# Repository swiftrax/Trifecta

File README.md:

# Trifecta

A 65% Alice with per key RGB, RGB backlighting and 3 rotary encoders. Designed by 2Moons-JP and swiftrax

# Render

# Proto Image

## License

This repository is under the [GNU GPL V2 license](https://github.com/swiftrax/Trifecta/blob/master/LICENSE). If you plan to sell these pcbs, make sure to read it.

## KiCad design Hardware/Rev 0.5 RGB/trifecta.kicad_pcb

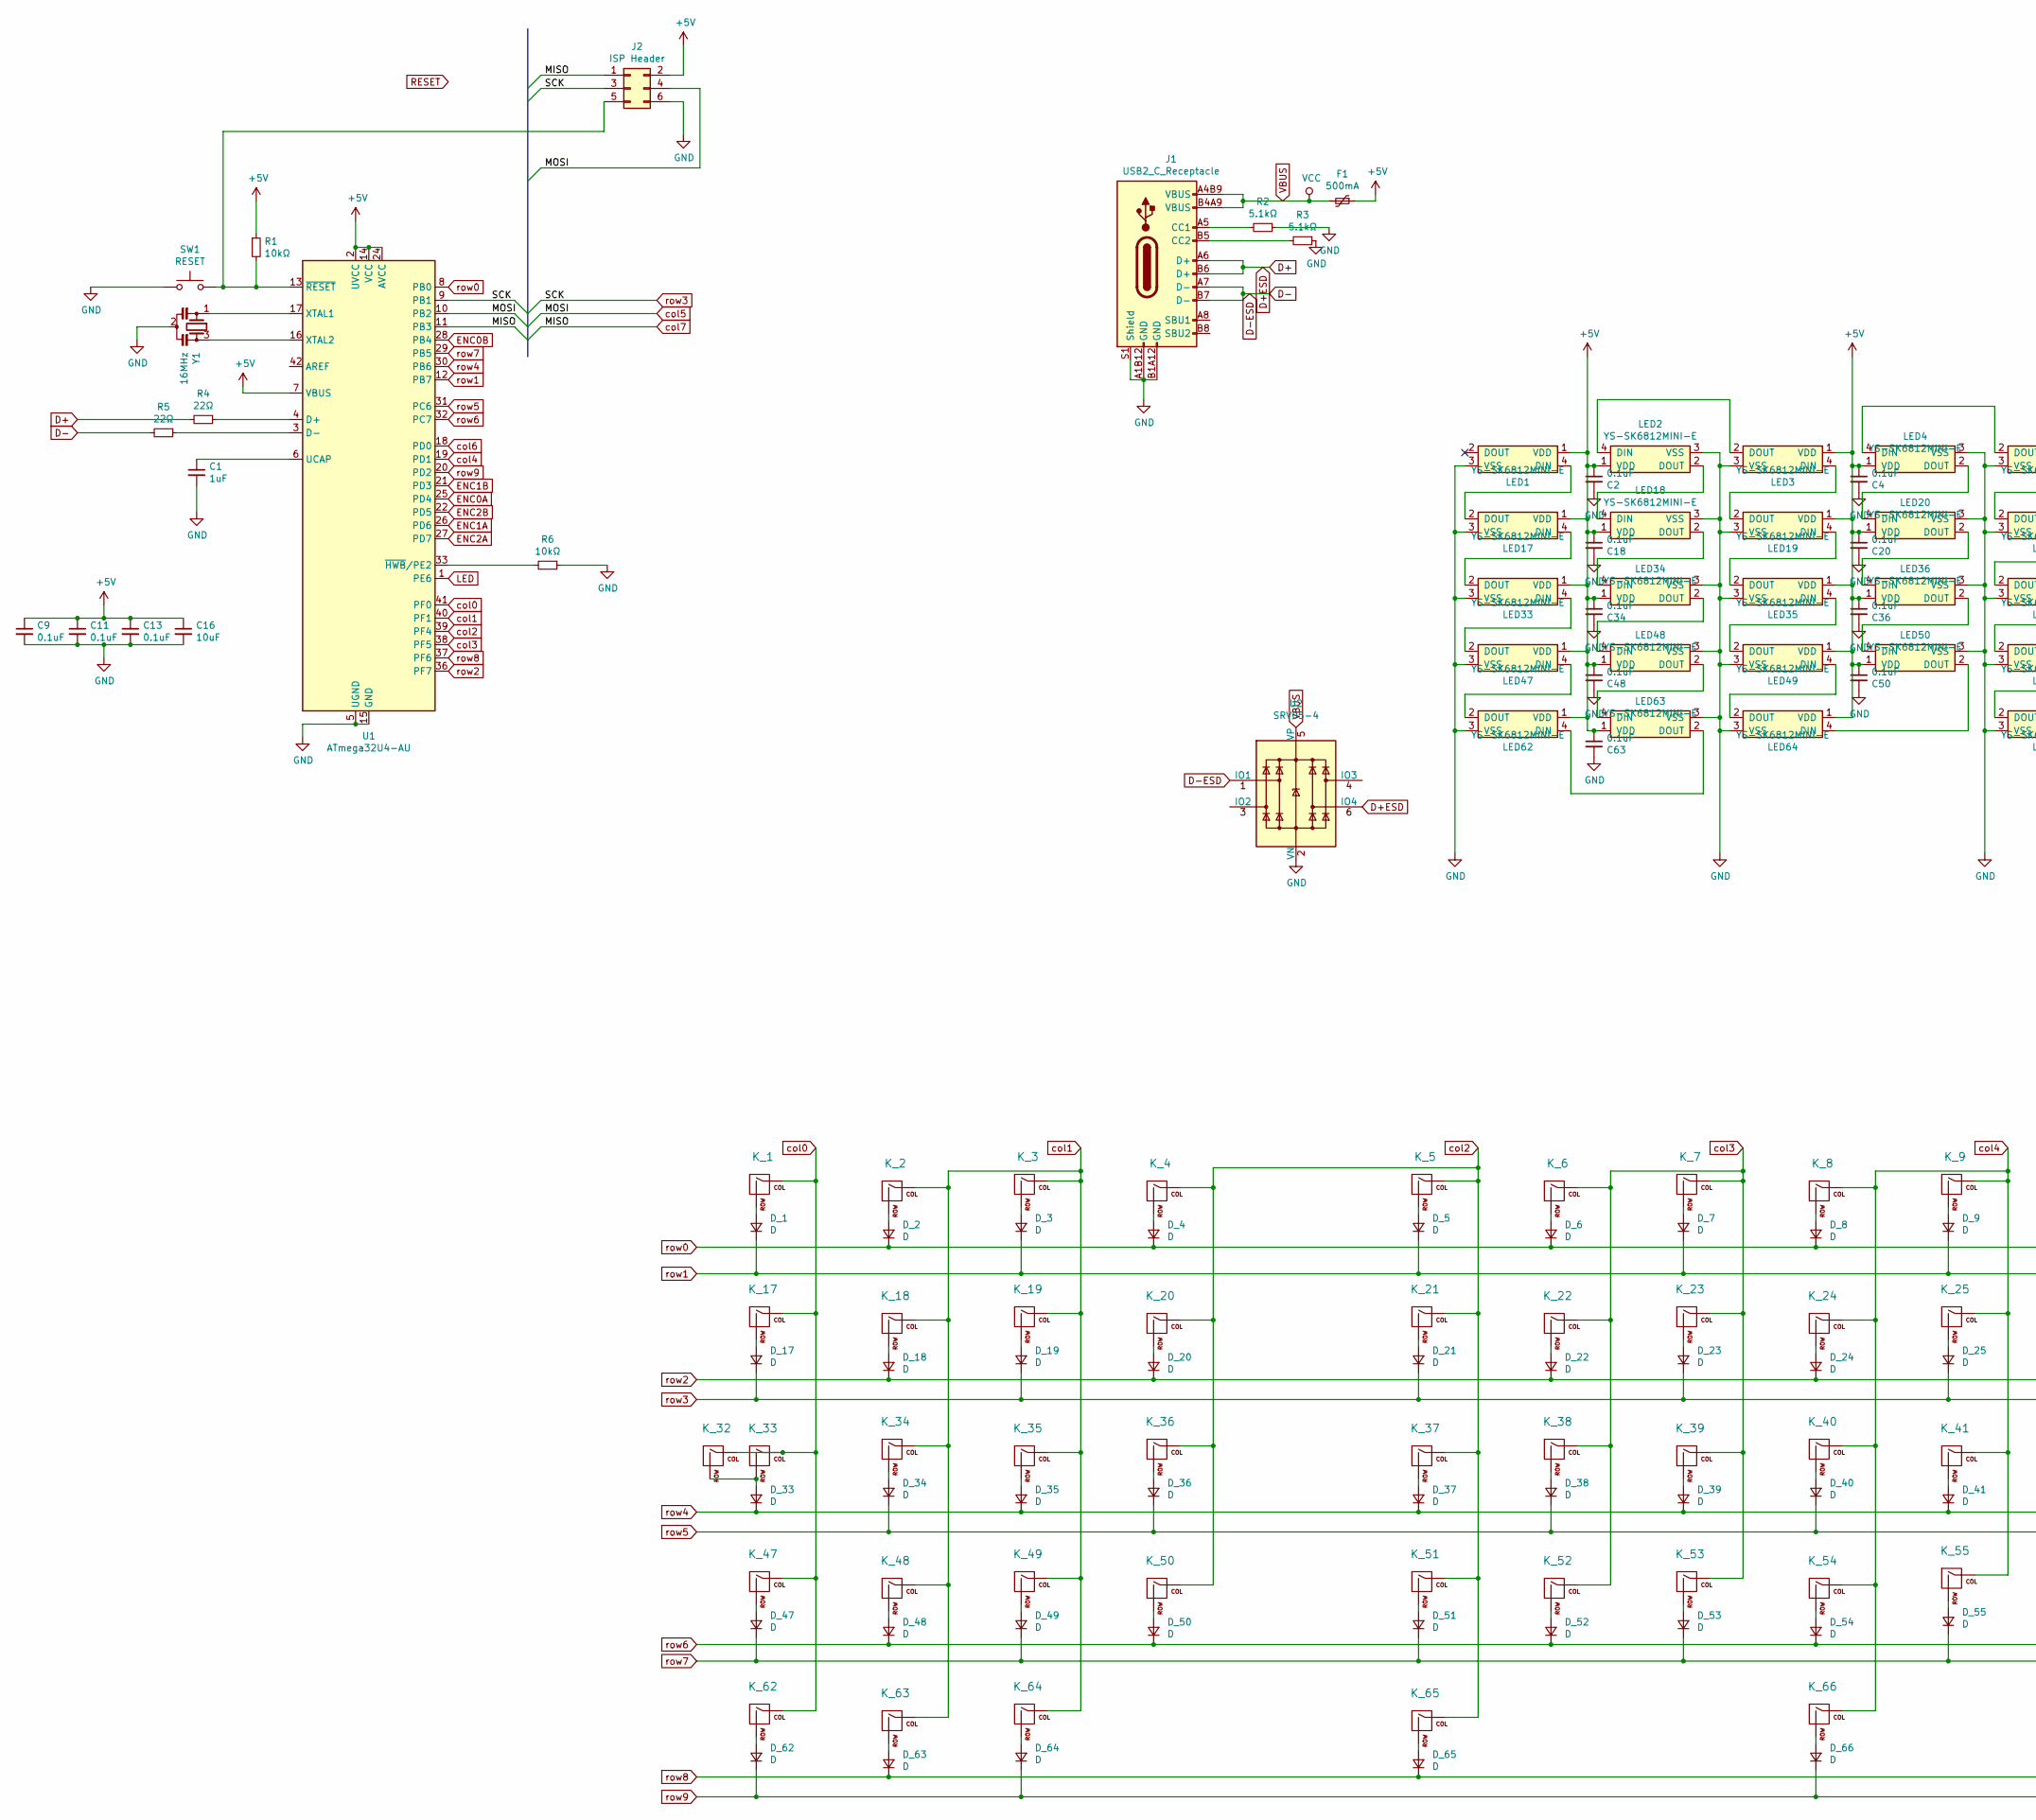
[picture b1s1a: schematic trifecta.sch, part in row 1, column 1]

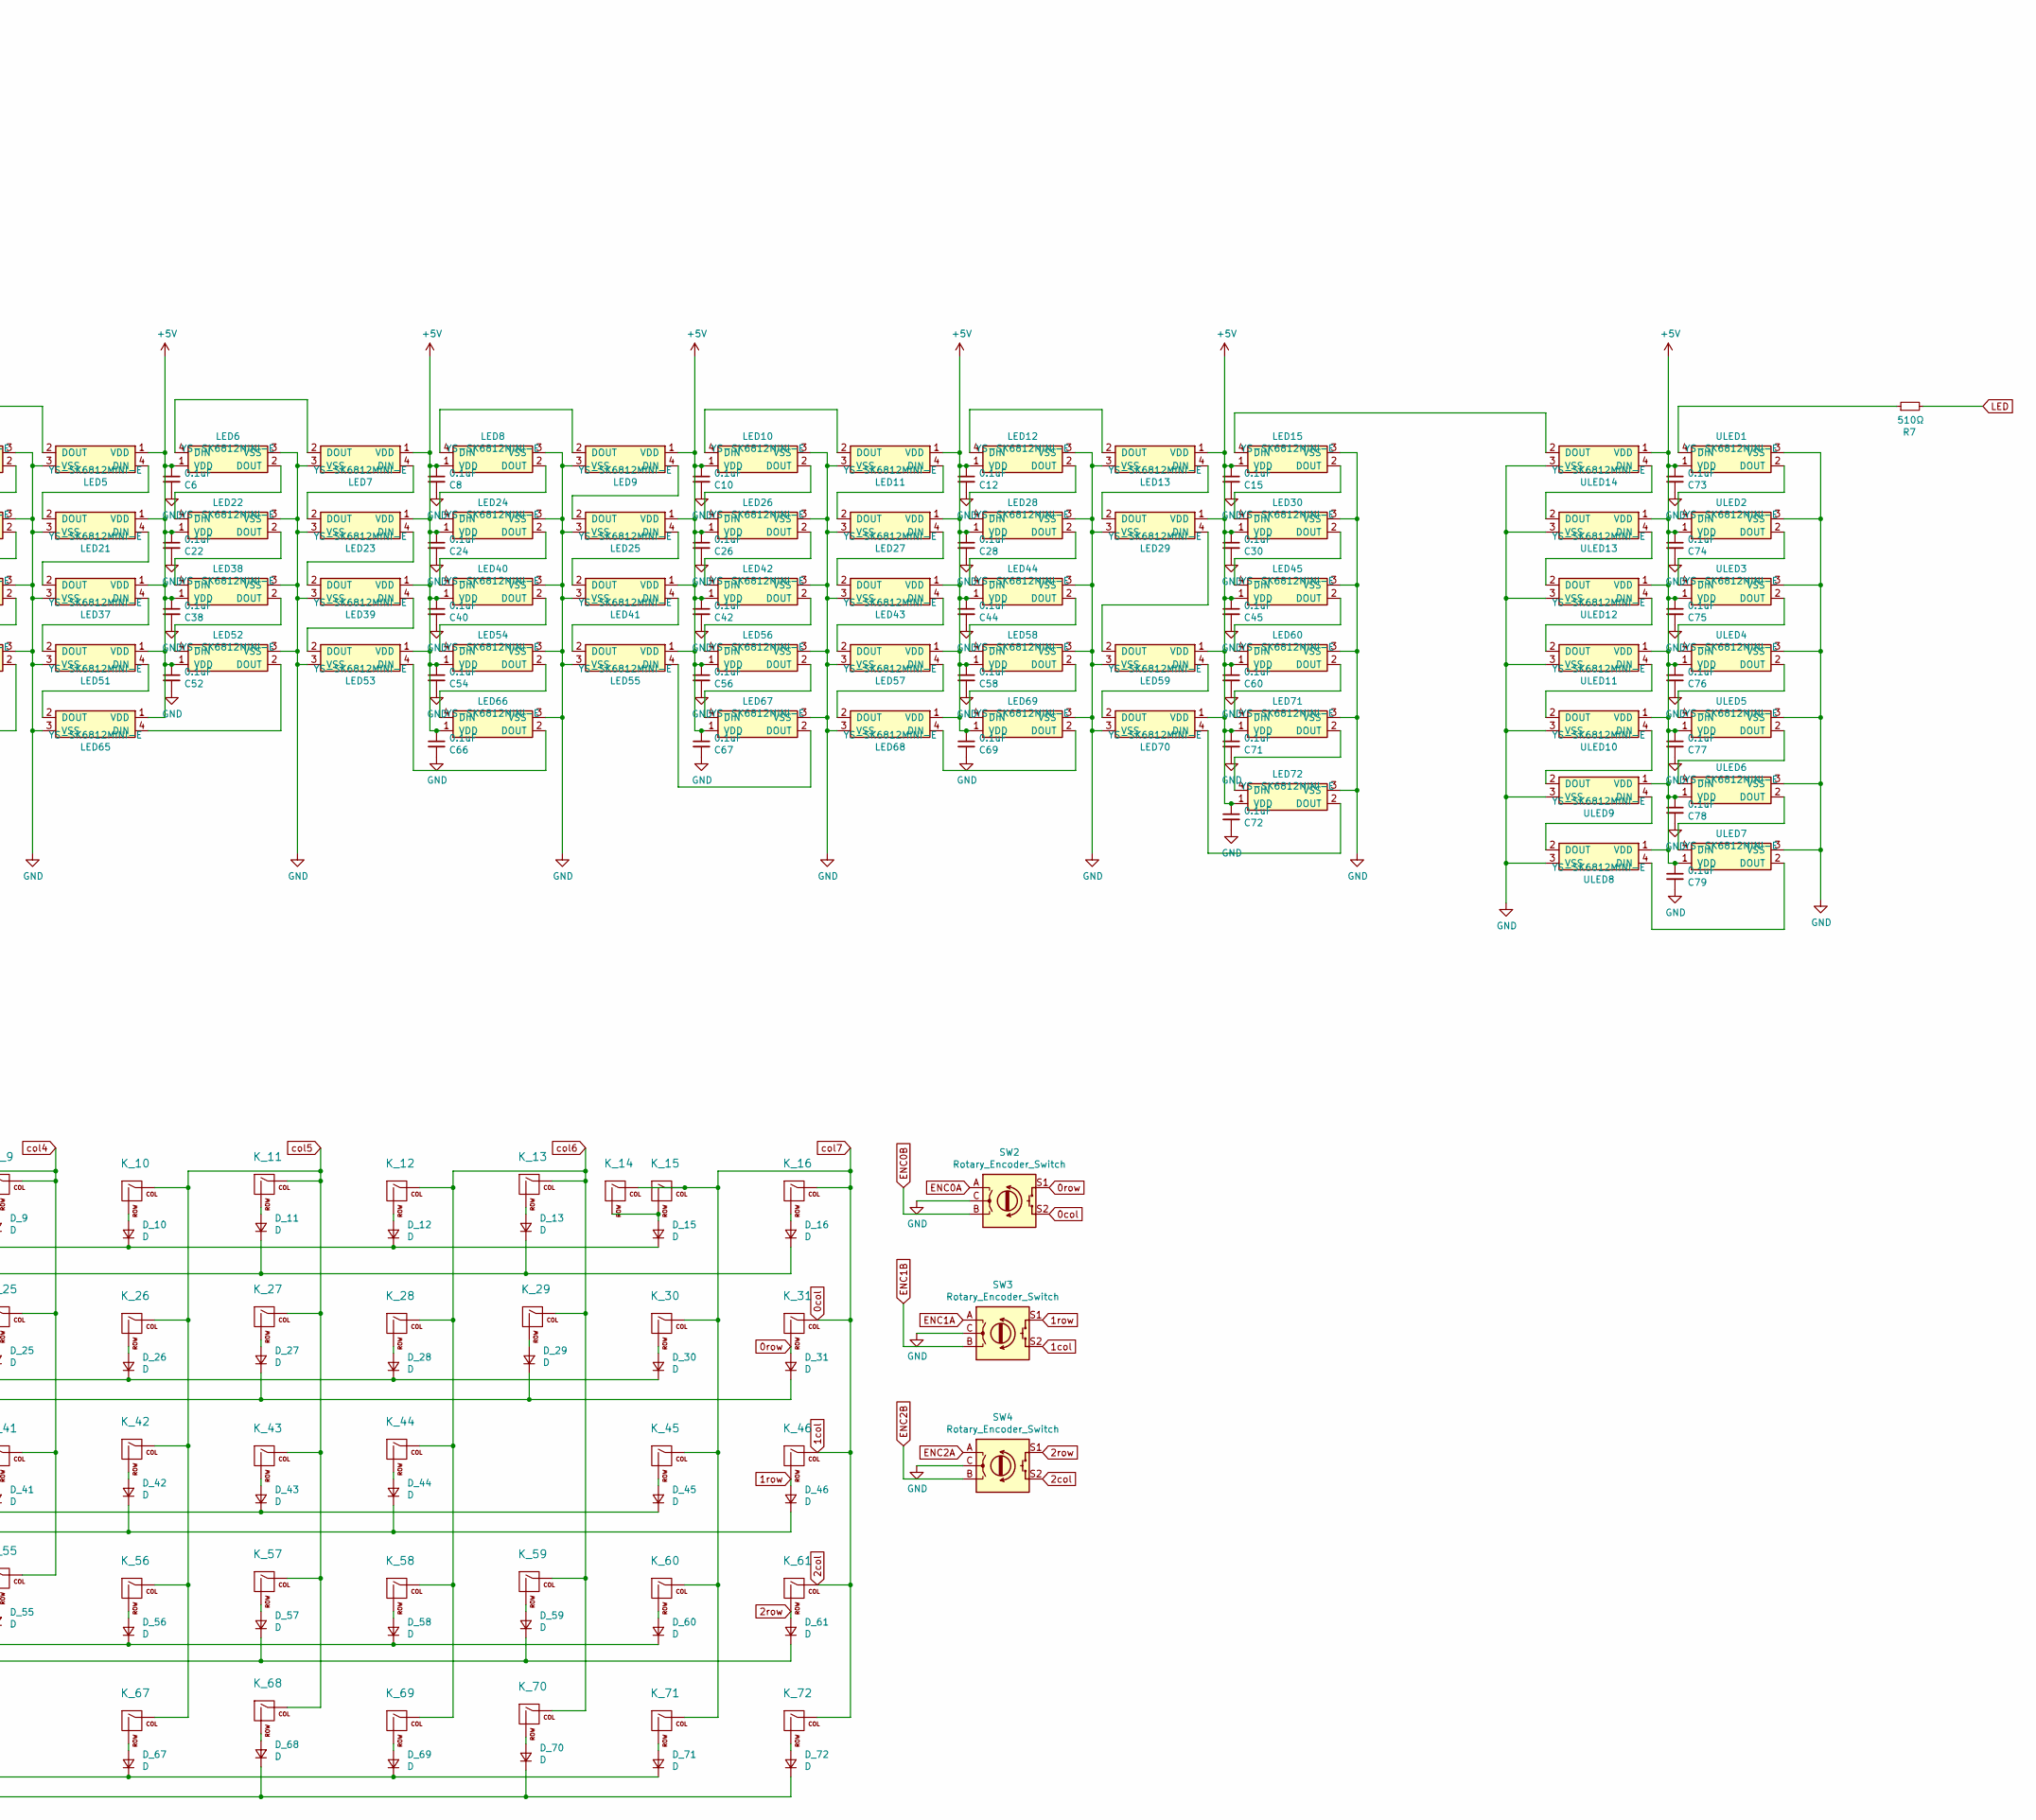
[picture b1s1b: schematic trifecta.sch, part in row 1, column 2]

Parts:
C1: 1uF; C_0805_2012Metric; Part# CL21B105KBFNNNE; LCSC Part# C28323
C2, C4, C6, C8, C9, C10, C11, C12, C13, C15, C18, C20, C22, C24, C26, C28, C30, C34, C36, C38, C40, C42, C44, C45, C48, C50, C52, C54, C56, C58, C60, C63, C66, C67, C69, C71, C72, C73, C74, C75, C76, C77, C78, C79: 0.1uF; C_0805_2012Metric; Part# CC0805KRX7R9BB104; LCSC Part# C49678
C16: 10uF; C_0805_2012Metric; Part# CL21A106KAYNNNE; LCSC Part# C15850
D_1, D_2, D_3, D_4, D_5, D_6, D_7, D_8, D_9, D_10, D_11, D_12, D_13, D_15, D_16, D_17, D_18, D_19, D_20, D_21, D_22, D_23, D_24, D_25, D_26, D_27, D_28, D_29, D_30, D_31, D_33, D_34, D_35, D_36, D_37, D_38, D_39, D_40, D_41, D_42, D_43, D_44, D_45, D_46, D_47, D_48, D_49, D_50, D_51, D_52, D_53, D_54, D_55, D_56, D_57, D_58, D_59, D_60, D_61, D_62, D_63, D_64, D_65, D_66, D_67, D_68, D_69, D_70, D_71, D_72: D; D3_SMD_v2; Part# 1N4148W; LCSC Part# C81598
F1: 500mA; Fuse_1206_3216Metric
J1: USB2_C_Receptacle; Mid_Mount-USB_C_HandSoldering
J2: ISP Header; PinHeader_2x03_P2.54mm_Vertical
K_1, K_2, K_3, K_4, K_5, K_6, K_7, K_8, K_9, K_10, K_11, K_12, K_13, K_14, K_16, K_18, K_19, K_20, K_21, K_22, K_23, K_24, K_25, K_26, K_27, K_28, K_29, K_30, K_31, K_34, K_35, K_36, K_37, K_38, K_39, K_40, K_41, K_42, K_43, K_44, K_46, K_48, K_49, K_50, K_51, K_52, K_53, K_54, K_55, K_56, K_57, K_58, K_60, K_61, K_70, K_71, K_72: KEYSW; MXOnly-1U-NoLED
K_15: KEYSW; MXOnly-2U-ReversedStabilizers-NoLED
K_17: KEYSW; MXOnly-1.5U-NoLED
K_32, K_33, K_59: KEYSW; MXOnly-1.75U-NoLED
K_45, K_47, K_66: KEYSW; MXOnly-2.25U-ReversedStabilizers-NoLED
K_62, K_63, K_64, K_67, K_68, K_69: KEYSW; MXOnly-1.25U-NoLED
K_65: KEYSW; MXOnly-2.75U-ReversedStabilizers-NoLED
LED1, LED2, LED3, LED4, LED5, LED6, LED7, LED8, LED9, LED10, LED11, LED12, LED13, LED15, LED17, LED18, LED19, LED20, LED21, LED22, LED23, LED24, LED25, LED26, LED27, LED28, LED29, LED30, LED33, LED34, LED35, LED36, LED37, LED38, LED39, LED40, LED41, LED42, LED43, LED44, LED45, LED47, LED48, LED49, LED50, LED51, LED52, LED53, LED54, LED55, LED56, LED57, LED58, LED59, LED60, LED62, LED63, LED64, LED65, LED66, LED67, LED68, LED69, LED70, LED71, LED72: YS-SK6812MINI-E
R1, R6: 10kΩ; R_0805_2012Metric; Part# 0805W8F1002T5E; LCSC Part# C17414
R2, R3: 5.1kΩ; R_0805_2012Metric; Part# 0805W8F5101T5E; LCSC Part# C27834
R4, R5: 22Ω; R_0805_2012Metric; Part# 0805W8F2202T5E; LCSC Part# C17560
R7: 510Ω; R_0805_2012Metric; Part# 0805W8F5100T5E; LCSC Part# C17734
SW1: RESET; SKQG-1155865
SW2, SW3, SW4: Rotary_Encoder_Switch; RotaryEncoder_EC11
U1: ATmega32U4-AU; ATMEGA32U4-AU; Part# ATMEGA32U4-AU; LCSC Part# C44854
U2: SRV05-4; SOT-23-6; Part# SRV05-4; LCSC Part# C127538
ULED1, ULED2, ULED3, ULED4, ULED5, ULED6, ULED7, ULED8, ULED9, ULED10, ULED11, ULED12, ULED13, ULED14: YS-SK6812MINI-E; Underglow YS-SK6812MINI-E
Y1: 16MHz; Resonator_SMD_muRata_CSTxExxV-3Pin_3.0x1.1mm_HandSoldering_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

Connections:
0col: J2.1, K_14.1 (COL), K_15.1 (COL), K_16.1 (COL), K_30.1 (COL), K_31.1 (COL), K_45.1 (COL), K_46.1 (COL), K_60.1 (COL), K_61.1 (COL), K_71.1 (COL), K_72.1 (COL), SW2.S2, SW3.S2, SW4.S2, U1.11 (PB3)
0row: D_31.2 (A), K_31.2 (ROW), SW2.S1
1row: D_46.2 (A), K_46.2 (ROW), SW3.S1
2row: D_61.2 (A), K_61.2 (ROW), SW4.S1
+5V: C2.1, C4.1, C6.1, C8.1, C9.1, C10.1, C11.1, C12.1, C13.1, C15.1, C16.1, C18.1, C20.1, C22.1, C24.1, C26.1, C28.1, C30.1, C34.1, C36.1, C38.1, C40.1, C42.1, C44.1, C45.1, C48.1, C50.1, C52.1, C54.1, C56.1, C58.1, C60.1, C63.1, C66.1, C67.1, C69.1, C71.1, C72.1, C73.1, C74.1, C75.1, C76.1, C77.1, C78.1, C79.1, F1.1, J2.2, LED1.1 (VDD), LED2.1 (VDD), LED3.1 (VDD), LED4.1 (VDD), LED5.1 (VDD), LED6.1 (VDD), LED7.1 (VDD), LED8.1 (VDD), LED9.1 (VDD), LED10.1 (VDD), LED11.1 (VDD), LED12.1 (VDD), LED13.1 (VDD), LED15.1 (VDD), LED17.1 (VDD), LED18.1 (VDD), LED19.1 (VDD), LED20.1 (VDD), LED21.1 (VDD), LED22.1 (VDD), LED23.1 (VDD), LED24.1 (VDD), LED25.1 (VDD), LED26.1 (VDD), LED27.1 (VDD), LED28.1 (VDD), LED29.1 (VDD), LED30.1 (VDD), LED33.1 (VDD), LED34.1 (VDD), LED35.1 (VDD), LED36.1 (VDD), LED37.1 (VDD), LED38.1 (VDD), LED39.1 (VDD), LED40.1 (VDD), LED41.1 (VDD), LED42.1 (VDD), LED43.1 (VDD), LED44.1 (VDD), LED45.1 (VDD), LED47.1 (VDD), LED48.1 (VDD), LED49.1 (VDD), LED50.1 (VDD), LED51.1 (VDD), LED52.1 (VDD), LED53.1 (VDD), LED54.1 (VDD), LED55.1 (VDD), LED56.1 (VDD), LED57.1 (VDD), LED58.1 (VDD), LED59.1 (VDD), LED60.1 (VDD), LED62.1 (VDD), LED63.1 (VDD), LED64.1 (VDD), LED65.1 (VDD), LED66.1 (VDD), LED67.1 (VDD), LED68.1 (VDD), LED69.1 (VDD), LED70.1 (VDD), LED71.1 (VDD), LED72.1 (VDD), R1.1, U1.2 (UVCC), U1.7 (VBUS), U1.14 (VCC), U1.24 (AVCC), U1.34 (VCC), U1.44 (AVCC), ULED1.1 (VDD), ULED2.1 (VDD), ULED3.1 (VDD), ULED4.1 (VDD), ULED5.1 (VDD), ULED6.1 (VDD), ULED7.1 (VDD), ULED8.1 (VDD), ULED9.1 (VDD), ULED10.1 (VDD), ULED11.1 (VDD), ULED12.1 (VDD), ULED13.1 (VDD), ULED14.1 (VDD)
D+: J1.A6 (D+), J1.B6 (D+), R4.2, U2.6 (IO4)
D-: J1.A7 (D-), J1.B7 (D-), R5.2, U2.1 (IO1)
ENC0A: SW2.A, U1.25 (PD4)
ENC0B: SW2.B, U1.28 (PB4)
ENC1A: SW3.A, U1.26 (PD6)
ENC1B: SW3.B, U1.21 (PD3)
ENC2A: SW4.A, U1.27 (PD7)
ENC2B: SW4.B, U1.22 (PD5)
GND: C1.2, C2.2, C4.2, C6.2, C8.2, C9.2, C10.2, C11.2, C12.2, C13.2, C15.2, C16.2, C18.2, C20.2, C22.2, C24.2, C26.2, C28.2, C30.2, C34.2, C36.2, C38.2, C40.2, C42.2, C44.2, C45.2, C48.2, C50.2, C52.2, C54.2, C56.2, C58.2, C60.2, C63.2, C66.2, C67.2, C69.2, C71.2, C72.2, C73.2, C74.2, C75.2, C76.2, C77.2, C78.2, C79.2, J1.A1B12 (GND), J1.B1A12 (GND), J1.S1 (Shield), J2.6, LED1.3 (VSS), LED2.3 (VSS), LED3.3 (VSS), LED4.3 (VSS), LED5.3 (VSS), LED6.3 (VSS), LED7.3 (VSS), LED8.3 (VSS), LED9.3 (VSS), LED10.3 (VSS), LED11.3 (VSS), LED12.3 (VSS), LED13.3 (VSS), LED15.3 (VSS), LED17.3 (VSS), LED18.3 (VSS), LED19.3 (VSS), LED20.3 (VSS), LED21.3 (VSS), LED22.3 (VSS), LED23.3 (VSS), LED24.3 (VSS), LED25.3 (VSS), LED26.3 (VSS), LED27.3 (VSS), LED28.3 (VSS), LED29.3 (VSS), LED30.3 (VSS), LED33.3 (VSS), LED34.3 (VSS), LED35.3 (VSS), LED36.3 (VSS), LED37.3 (VSS), LED38.3 (VSS), LED39.3 (VSS), LED40.3 (VSS), LED41.3 (VSS), LED42.3 (VSS), LED43.3 (VSS), LED44.3 (VSS), LED45.3 (VSS), LED47.3 (VSS), LED48.3 (VSS), LED49.3 (VSS), LED50.3 (VSS), LED51.3 (VSS), LED52.3 (VSS), LED53.3 (VSS), LED54.3 (VSS), LED55.3 (VSS), LED56.3 (VSS), LED57.3 (VSS), LED58.3 (VSS), LED59.3 (VSS), LED60.3 (VSS), LED62.3 (VSS), LED63.3 (VSS), LED64.3 (VSS), LED65.3 (VSS), LED66.3 (VSS), LED67.3 (VSS), LED68.3 (VSS), LED69.3 (VSS), LED70.3 (VSS), LED71.3 (VSS), LED72.3 (VSS), R2.1, R3.1, R6.1, SW1.1, SW2.C, SW3.C, SW4.C, U1.5 (UGND), U1.15 (GND), U1.23 (GND), U1.35 (GND), U1.43 (GND), U2.2 (VN), ULED1.3 (VSS), ULED2.3 (VSS), ULED3.3 (VSS), ULED4.3 (VSS), ULED5.3 (VSS), ULED6.3 (VSS), ULED7.3 (VSS), ULED8.3 (VSS), ULED9.3 (VSS), ULED10.3 (VSS), ULED11.3 (VSS), ULED12.3 (VSS), ULED13.3 (VSS), ULED14.3 (VSS), Y1.2
LED: R7.2, U1.1 (PE6)
unnamed: C1.1, U1.6 (UCAP)
unnamed: D_1.2 (A), K_1.2 (ROW)
unnamed: D_2.2 (A), K_2.2 (ROW)
unnamed: D_3.2 (A), K_3.2 (ROW)
unnamed: D_4.2 (A), K_4.2 (ROW)
unnamed: D_5.2 (A), K_5.2 (ROW)
unnamed: D_6.2 (A), K_6.2 (ROW)
unnamed: D_7.2 (A), K_7.2 (ROW)
unnamed: D_8.2 (A), K_8.2 (ROW)
unnamed: D_9.2 (A), K_9.2 (ROW)
unnamed: D_10.2 (A), K_10.2 (ROW)
unnamed: D_11.2 (A), K_11.2 (ROW)
unnamed: D_12.2 (A), K_12.2 (ROW)
unnamed: D_13.2 (A), K_13.2 (ROW)
unnamed: D_15.2 (A), K_14.2 (ROW), K_15.2 (ROW)
unnamed: D_16.2 (A), K_16.2 (ROW)
unnamed: D_17.2 (A), K_17.2 (ROW)
unnamed: D_18.2 (A), K_18.2 (ROW)
unnamed: D_19.2 (A), K_19.2 (ROW)
unnamed: D_20.2 (A), K_20.2 (ROW)
unnamed: D_21.2 (A), K_21.2 (ROW)
unnamed: D_22.2 (A), K_22.2 (ROW)
unnamed: D_23.2 (A), K_23.2 (ROW)
unnamed: D_24.2 (A), K_24.2 (ROW)
unnamed: D_25.2 (A), K_25.2 (ROW)
unnamed: D_26.2 (A), K_26.2 (ROW)
unnamed: D_27.2 (A), K_27.2 (ROW)
unnamed: D_28.2 (A), K_28.2 (ROW)
unnamed: D_29.2 (A), K_29.2 (ROW)
unnamed: D_30.2 (A), K_30.2 (ROW)
unnamed: D_33.2 (A), K_32.2 (ROW), K_33.2 (ROW)
unnamed: D_34.2 (A), K_34.2 (ROW)
unnamed: D_35.2 (A), K_35.2 (ROW)
unnamed: D_36.2 (A), K_36.2 (ROW)
unnamed: D_37.2 (A), K_37.2 (ROW)
unnamed: D_38.2 (A), K_38.2 (ROW)
unnamed: D_39.2 (A), K_39.2 (ROW)
unnamed: D_40.2 (A), K_40.2 (ROW)
unnamed: D_41.2 (A), K_41.2 (ROW)
unnamed: D_42.2 (A), K_42.2 (ROW)
unnamed: D_43.2 (A), K_43.2 (ROW)
unnamed: D_44.2 (A), K_44.2 (ROW)
unnamed: D_45.2 (A), K_45.2 (ROW)
unnamed: D_47.2 (A), K_47.2 (ROW)
unnamed: D_48.2 (A), K_48.2 (ROW)
unnamed: D_49.2 (A), K_49.2 (ROW)
unnamed: D_50.2 (A), K_50.2 (ROW)
unnamed: D_51.2 (A), K_51.2 (ROW)
unnamed: D_52.2 (A), K_52.2 (ROW)
unnamed: D_53.2 (A), K_53.2 (ROW)
unnamed: D_54.2 (A), K_54.2 (ROW)
unnamed: D_55.2 (A), K_55.2 (ROW)
unnamed: D_56.2 (A), K_56.2 (ROW)
unnamed: D_57.2 (A), K_57.2 (ROW)
unnamed: D_58.2 (A), K_58.2 (ROW)
unnamed: D_59.2 (A), K_59.2 (ROW)
unnamed: D_60.2 (A), K_60.2 (ROW)
unnamed: D_62.2 (A), K_62.2 (ROW)
unnamed: D_63.2 (A), K_63.2 (ROW)
unnamed: D_64.2 (A), K_64.2 (ROW)
unnamed: D_65.2 (A), K_65.2 (ROW)
unnamed: D_66.2 (A), K_66.2 (ROW)
unnamed: D_67.2 (A), K_67.2 (ROW)
unnamed: D_68.2 (A), K_68.2 (ROW)
unnamed: D_69.2 (A), K_69.2 (ROW)
unnamed: D_70.2 (A), K_70.2 (ROW)
unnamed: D_71.2 (A), K_71.2 (ROW)
unnamed: D_72.2 (A), K_72.2 (ROW)
unnamed: J1.A5 (CC1), R2.2
unnamed: J1.B5 (CC2), R3.2
unnamed: J2.5, R1.2, SW1.2, U1.13 (~RESET)
unnamed: LED1.4 (DIN), LED17.2 (DOUT)
unnamed: LED2.4 (DIN), LED3.2 (DOUT)
unnamed: LED4.4 (DIN), LED5.2 (DOUT)
unnamed: LED6.4 (DIN), LED7.2 (DOUT)
unnamed: LED8.4 (DIN), LED9.2 (DOUT)
unnamed: LED10.2 (DOUT), LED26.4 (DIN)
unnamed: LED10.4 (DIN), LED11.2 (DOUT)
unnamed: LED11.4 (DIN), LED27.2 (DOUT)
unnamed: LED12.2 (DOUT), LED28.4 (DIN)
unnamed: LED12.4 (DIN), LED13.2 (DOUT)
unnamed: LED13.4 (DIN), LED29.2 (DOUT)
unnamed: LED15.2 (DOUT), LED30.4 (DIN)
unnamed: LED15.4 (DIN), ULED14.2 (DOUT)
unnamed: LED17.4 (DIN), LED33.2 (DOUT)
unnamed: LED18.2 (DOUT), LED34.4 (DIN)
unnamed: LED2.2 (DOUT), LED18.4 (DIN)
unnamed: LED3.4 (DIN), LED19.2 (DOUT)
unnamed: LED19.4 (DIN), LED35.2 (DOUT)
unnamed: LED20.2 (DOUT), LED36.4 (DIN)
unnamed: LED4.2 (DOUT), LED20.4 (DIN)
unnamed: LED5.4 (DIN), LED21.2 (DOUT)
unnamed: LED21.4 (DIN), LED37.2 (DOUT)
unnamed: LED22.2 (DOUT), LED38.4 (DIN)
unnamed: LED6.2 (DOUT), LED22.4 (DIN)
unnamed: LED7.4 (DIN), LED23.2 (DOUT)
unnamed: LED23.4 (DIN), LED39.2 (DOUT)
unnamed: LED24.2 (DOUT), LED40.4 (DIN)
unnamed: LED8.2 (DOUT), LED24.4 (DIN)
unnamed: LED9.4 (DIN), LED25.2 (DOUT)
unnamed: LED25.4 (DIN), LED41.2 (DOUT)
unnamed: LED26.2 (DOUT), LED42.4 (DIN)
unnamed: LED27.4 (DIN), LED43.2 (DOUT)
unnamed: LED28.2 (DOUT), LED44.4 (DIN)
unnamed: LED29.4 (DIN), LED59.2 (DOUT)
unnamed: LED30.2 (DOUT), LED45.4 (DIN)
unnamed: LED33.4 (DIN), LED47.2 (DOUT)
unnamed: LED34.2 (DOUT), LED48.4 (DIN)
unnamed: LED35.4 (DIN), LED49.2 (DOUT)
unnamed: LED36.2 (DOUT), LED50.4 (DIN)
unnamed: LED37.4 (DIN), LED51.2 (DOUT)
unnamed: LED38.2 (DOUT), LED52.4 (DIN)
unnamed: LED39.4 (DIN), LED53.2 (DOUT)
unnamed: LED40.2 (DOUT), LED54.4 (DIN)
unnamed: LED41.4 (DIN), LED55.2 (DOUT)
unnamed: LED42.2 (DOUT), LED56.4 (DIN)
unnamed: LED43.4 (DIN), LED57.2 (DOUT)
unnamed: LED44.2 (DOUT), LED58.4 (DIN)
unnamed: LED45.2 (DOUT), LED60.4 (DIN)
unnamed: LED47.4 (DIN), LED62.2 (DOUT)
unnamed: LED48.2 (DOUT), LED63.4 (DIN)
unnamed: LED49.4 (DIN), LED64.2 (DOUT)
unnamed: LED50.2 (DOUT), LED64.4 (DIN)
unnamed: LED51.4 (DIN), LED65.2 (DOUT)
unnamed: LED52.2 (DOUT), LED65.4 (DIN)
unnamed: LED53.4 (DIN), LED66.2 (DOUT)
unnamed: LED54.2 (DOUT), LED66.4 (DIN)
unnamed: LED55.4 (DIN), LED67.2 (DOUT)
unnamed: LED56.2 (DOUT), LED67.4 (DIN)
unnamed: LED57.4 (DIN), LED68.2 (DOUT)
unnamed: LED58.2 (DOUT), LED69.4 (DIN)
unnamed: LED59.4 (DIN), LED70.2 (DOUT)
unnamed: LED60.2 (DOUT), LED71.4 (DIN)
unnamed: LED62.4 (DIN), LED63.2 (DOUT)
unnamed: LED68.4 (DIN), LED69.2 (DOUT)
unnamed: LED70.4 (DIN), LED72.2 (DOUT)
unnamed: LED71.2 (DOUT), LED72.4 (DIN)
unnamed: R4.1, U1.4 (D+)
unnamed: R5.1, U1.3 (D-)
unnamed: R6.2, U1.33 (~HWB~/PE2)
unnamed: R7.1, ULED1.4 (DIN)
unnamed: U1.16 (XTAL2), Y1.3
unnamed: U1.17 (XTAL1), Y1.1
unnamed: ULED1.2 (DOUT), ULED2.4 (DIN)
unnamed: ULED2.2 (DOUT), ULED3.4 (DIN)
unnamed: ULED3.2 (DOUT), ULED4.4 (DIN)
unnamed: ULED4.2 (DOUT), ULED5.4 (DIN)
unnamed: ULED5.2 (DOUT), ULED6.4 (DIN)
unnamed: ULED6.2 (DOUT), ULED7.4 (DIN)
unnamed: ULED7.2 (DOUT), ULED8.4 (DIN)
unnamed: ULED8.2 (DOUT), ULED9.4 (DIN)
unnamed: ULED10.2 (DOUT), ULED11.4 (DIN)
unnamed: ULED9.2 (DOUT), ULED10.4 (DIN)
unnamed: ULED11.2 (DOUT), ULED12.4 (DIN)
unnamed: ULED12.2 (DOUT), ULED13.4 (DIN)
unnamed: ULED13.2 (DOUT), ULED14.4 (DIN)
VBUS: F1.2, J1.A4B9 (VBUS), J1.B4A9 (VBUS), U2.5 (VP)
col0: K_1.1 (COL), K_17.1 (COL), K_32.1 (COL), K_33.1 (COL), K_47.1 (COL), K_62.1 (COL), U1.41 (PF0)
col1: K_2.1 (COL), K_3.1 (COL), K_18.1 (COL), K_19.1 (COL), K_34.1 (COL), K_35.1 (COL), K_48.1 (COL), K_49.1 (COL), K_63.1 (COL), K_64.1 (COL), U1.40 (PF1)
col2: K_4.1 (COL), K_5.1 (COL), K_20.1 (COL), K_21.1 (COL), K_36.1 (COL), K_37.1 (COL), K_50.1 (COL), K_51.1 (COL), K_65.1 (COL), U1.39 (PF4)
col3: K_6.1 (COL), K_7.1 (COL), K_22.1 (COL), K_23.1 (COL), K_38.1 (COL), K_39.1 (COL), K_52.1 (COL), K_53.1 (COL), U1.38 (PF5)
col4: K_8.1 (COL), K_9.1 (COL), K_24.1 (COL), K_25.1 (COL), K_40.1 (COL), K_41.1 (COL), K_54.1 (COL), K_55.1 (COL), K_66.1 (COL), U1.19 (PD1)
col5: J2.4, K_10.1 (COL), K_11.1 (COL), K_26.1 (COL), K_27.1 (COL), K_42.1 (COL), K_43.1 (COL), K_56.1 (COL), K_57.1 (COL), K_67.1 (COL), K_68.1 (COL), U1.10 (PB2)
col6: K_12.1 (COL), K_13.1 (COL), K_28.1 (COL), K_29.1 (COL), K_44.1 (COL), K_58.1 (COL), K_59.1 (COL), K_69.1 (COL), K_70.1 (COL), U1.18 (PD0)
row0: D_2.1 (K), D_4.1 (K), D_6.1 (K), D_8.1 (K), D_10.1 (K), D_12.1 (K), D_15.1 (K), U1.8 (PB0)
row1: D_1.1 (K), D_3.1 (K), D_5.1 (K), D_7.1 (K), D_9.1 (K), D_11.1 (K), D_13.1 (K), D_16.1 (K), U1.12 (PB7)
row2: D_18.1 (K), D_20.1 (K), D_22.1 (K), D_24.1 (K), D_26.1 (K), D_28.1 (K), D_30.1 (K), U1.36 (PF7)
row3: D_17.1 (K), D_19.1 (K), D_21.1 (K), D_23.1 (K), D_25.1 (K), D_27.1 (K), D_29.1 (K), D_31.1 (K), J2.3, U1.9 (PB1)
row4: D_33.1 (K), D_35.1 (K), D_37.1 (K), D_39.1 (K), D_41.1 (K), D_43.1 (K), D_45.1 (K), U1.30 (PB6)
row5: D_34.1 (K), D_36.1 (K), D_38.1 (K), D_40.1 (K), D_42.1 (K), D_44.1 (K), D_46.1 (K), U1.31 (PC6)
row6: D_48.1 (K), D_50.1 (K), D_52.1 (K), D_54.1 (K), D_56.1 (K), D_58.1 (K), D_60.1 (K), U1.32 (PC7)
row7: D_47.1 (K), D_49.1 (K), D_51.1 (K), D_53.1 (K), D_55.1 (K), D_57.1 (K), D_59.1 (K), D_61.1 (K), U1.29 (PB5)
row8: D_63.1 (K), D_65.1 (K), D_67.1 (K), D_69.1 (K), D_71.1 (K), U1.37 (PF6)
row9: D_62.1 (K), D_64.1 (K), D_66.1 (K), D_68.1 (K), D_70.1 (K), D_72.1 (K), U1.20 (PD2)

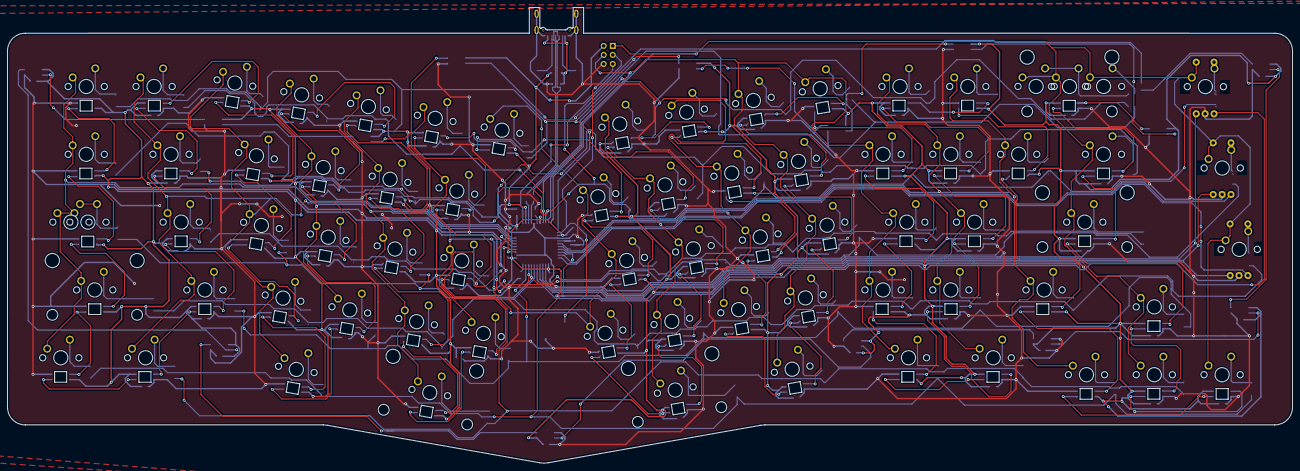
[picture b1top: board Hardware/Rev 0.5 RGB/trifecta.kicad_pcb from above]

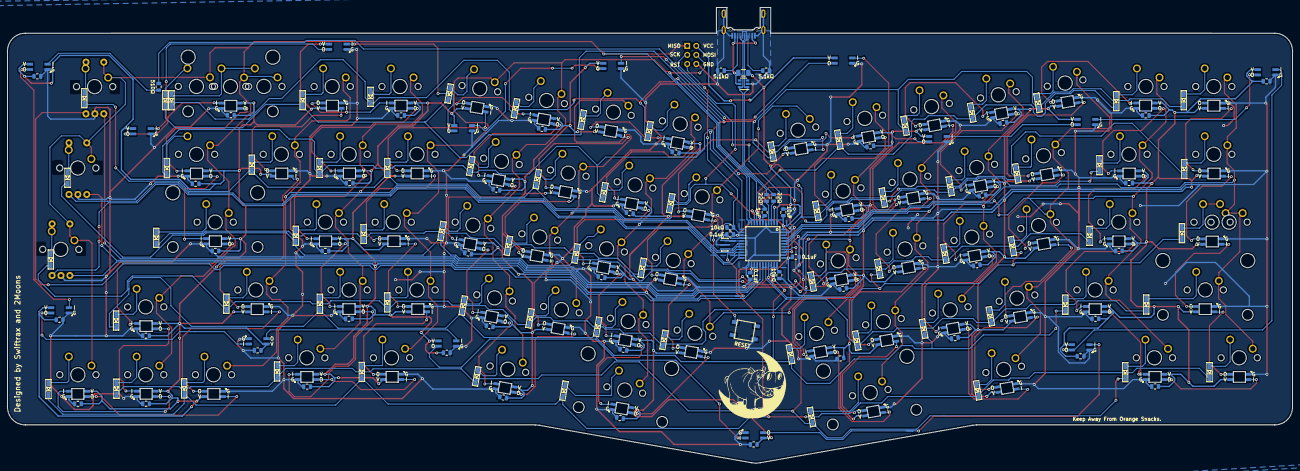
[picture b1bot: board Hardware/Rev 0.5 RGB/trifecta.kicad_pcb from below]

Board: 2 copper layers, 361.0 x 128.0 mm, 285 parts (210 on the bottom side), 189 nets.
